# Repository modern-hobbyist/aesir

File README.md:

# Project Aesir: Custom Keyboard PCB Designs

> ** Many of these boards are still works in progress **

**Project Aesir** is a collection of custom keyboard PCB designs created using KiCad, aimed at keyboard enthusiasts and DIY makers. Each project in this collection was designed to scratch a specific itch, fill a need, or address a particular problem I had with traditional mechanical keyboards, from a template for a standard keyboard PCB using the STM32F072CBT6 microcontroller to a split ergonomic keyboard design with a modular numpad.

I initially started this collection as a personal respository of templates to get my new projects on the ground running faster, but it has gradually grown to include several board designs I've completed. Make sure to check back in periodically as I add new boards to my collection!

## Included Projects
1. **Heimdall**: A full-sized keyboard PCB designed for customization and personal use.
2. **Hermod**: A split ergonomic keyboard design for those seeking an ergonomic, portable build. Featuring a magnetically detachable AND reversible numpad!
3. **Hermod Mk. II**: A remake of the original Hermod with an upgraded STM32G474CET6 MCU, supporting Choc V2 and Gateron KS-33 low profile switches. Including an updated thumb cluster for better ergonomics and an extra key.
3. **Hermod Mk. II - MX**: A remake of the original Hermod, this time with **MX Spacing**. Same as *8Hermod Mk. II** -- supporting Choc V2 and Gateron KS-33 switches.
4. **Hermod Mk. II - MX - North**: Same as **Hermod Mk. II - MX** but with North facing switches for better shine through keycap legend appearance.
5. **Hermod Mk. III**: A continuation of **Hermod Mk. II - MX - North** with several component upgrades for easier/cheaper sourcing (e.g. SRV05-4 for ESD).
6. **Mist**: A full sized keyboard with a new take on the spacebar--replacing it with thumb clusters. It also supports Cherry MX/Gateron Normal Profile or Gateron KS-33 Low Profile Switches.
7. **Mist UDB**: Same as **Mist**, but using a unified daughter board to offload the ESD and USB protection.
8. **Mist UDB - Mk. II**: Same as **Mist UDB** but with proper support for the Gateron Low profile stabilizers as well as standard PCB mount stabilizers via mousebitten PCB cutouts.
3. **STM32F072CBT6 Standard Template**: A blank template for creating your own keyboard designs with the STM32F072CBT6 microcontroller.
4. **STM32F072CBT6 Split Template**: A blank template for creating your own split keyboard designs with the STM32F072CBT6 microcontroller.

## Getting Started

> Note: There may be footprints I've created or manually altered that aren't packaged with this repository, so if you come across something missing, please create an issue and I'll get it updated!

### Requirements
- **KiCad**: Download and install the latest version of [KiCad](https://www.kicad.org/download/).
- **PCB Manufacturer**: These projects were developed in collaboration with PCBWay. Each sub-project will have a link to the project on PCBWay's project sharing platform so you can order them with the click of a button.
- **Plugins**: There are a few KiCad plugins that you can install that will help with building these PCB's as well as one library of keyswitches:
  - [marbastlib Keyswitch Symbol Library](https://github.com/ebastler/marbastlib)
  - [kicad-kbplacer](https://github.com/adamws/kicad-kbplacer)
  - [PCBWay Order Plugin](https://github.com/pcbway/PCBWay-Plug-in-for-Kicad)

### Steps
1. Clone this repository to your local machine.
    ```bash
    git clone https://github.com/modern-hobbyist/aesir
    ```
2. Open the desired KiCad project in your KiCad software.
3. Customize the layout, add your own components, and make any modifications to fit your needs.
4. Export the Gerber files for your chosen PCB manufacturer.
5. Build and assemble your keyboard!

## Contributing
Contributions to **Project Aesir** are welcome! Whether it's improving existing designs, adding new features, or creating entirely new layouts, feel free to open a pull request.

### Contribution Guidelines
1. Fork the repository.
2. Make your changes on a new branch.
3. Submit a pull request with a clear description of your contribution.

## Disclaimer
These designs are provided as-is, without warranty of any kind. I am not liable for any damages, malfunctions, or issues that may arise from using or modifying these designs, including but not limited to hardware damage, injury, or other unintended consequences. By using these designs, you agree to take full responsibility for any results, modifications, or assembly errors.

## License
This project is licensed under the MIT License. See the [LICENSE](LICENSE) file for details.

## Contact
For questions or collaboration inquiries, feel free to create an issue, reach out to me on GitHub or Discord or via my [YouTube channel](https://www.youtube.com/ModernHobbyist).

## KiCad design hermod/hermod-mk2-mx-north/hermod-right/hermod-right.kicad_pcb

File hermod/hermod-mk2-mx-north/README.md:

# Hermod Mk. II - North

> **Note:** This PCB is untested. I made updates to this design to address issues I had with the previous version, but I haven't ordered boards, nor have I written the matching firmware for it.

Hermod Mk. II is a redesign of my original Hermod split keyboard, which in turn was my second keyboard design ever! Some issues that were resolved in this version include:
- Better Pin choices for PWM Channels, Mk. I had some issues with timers overlapping
- Added a handedness pin 
  - Allows me to avoid using flash to store handedness
- Switched to Full Duplex split comms
- Mk.I was missing a 5.1kΩ resistor on the split serial line and this switched fixes that.
- Switched to `STM32G474CETx` from the `STM32F072CBT6`
  - More Ram, more flash, more fun. Didn't have enough ram for fun graphics on the LCD
- Added PWM Backlight control for the LCD Display 

Furthermore, this is the **NORTH FACING** MX Spacing variant. While it is functionally identically to the Hermod Mk. II, this layout is spaced in a 19.05x19.05 grid, which makes it compatible with the [Tai-Hao keycaps](https://shop.tai-hao.com/products/98white-1) highlighted in the ZSA Voyager. Also, the switches are rotated 180• from the previous versions so that the LED's are better aligned with shine-through keycaps. 

## Features

- **Split Design**: Ergonomic split layout for improved typing comfort.
- **Detachable Numpad**: Magnetically detachable and reversible numpad that can connect to either half.
- **Dual LCD Displays**: Each half features a 2.2" LCD for customizable graphics and real-time information.
- **QMK Firmware**: Fully programmable and customizable using QMK.
- **Per-Key RGB Lighting**: Vibrant, individually addressable RGB LEDs for endless customization.
- **Hot-Swappable Switch Sockets**: Easily swap out switches without soldering.
- **Open Source Hardware**: Schematics and design files available for personal customization.

## Specifications

- **Microcontroller**: STM32G474CETx
- **Key Layout**: Split layout with additional keys for layers and macros.
- **Display**: 2.2" LCD (320x240 resolution) per half.
- **Lighting**: SK6812 Mini RGB LEDs.
- **Switches**: Kailh Choc Low Profile.

## Issues
- 1.5u Footprint Solder Mask Layer missing (fixed)
  - Caused one of the pads for the 1.5u switches to be covered with Solder Mask
- LCD SD Card Pins Intersecting USB Data lines (fixed)
  - I accidentally updated the LCD footprint and didn't run DRC so the data lines had LCD SD card pins running right through them.

## License

This project is licensed under the MIT License. See the [LICENSE](../LICENSE) file for details.

## Acknowledgments

- The QMK community for their amazing firmware.
- Adafruit for the GFX library support.
- Inspiration from the mechanical keyboard enthusiast community.

---

For more information, check out the [Modern Hobbyist YouTube channel](https://www.youtube.com/ModernHobbyist) for videos about this project!

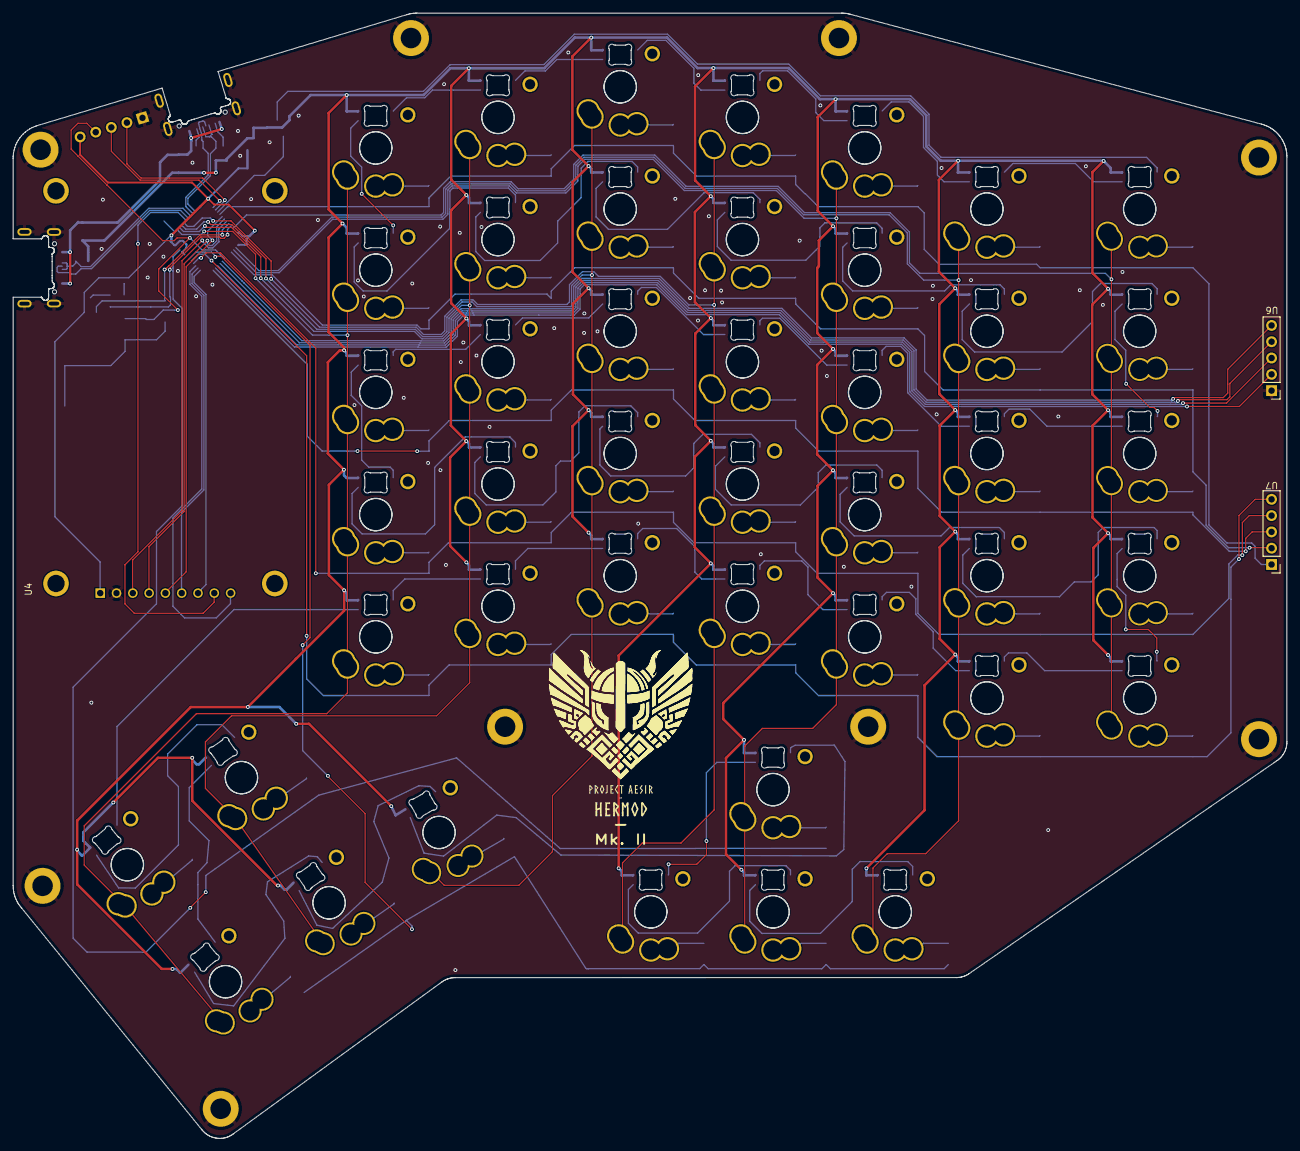
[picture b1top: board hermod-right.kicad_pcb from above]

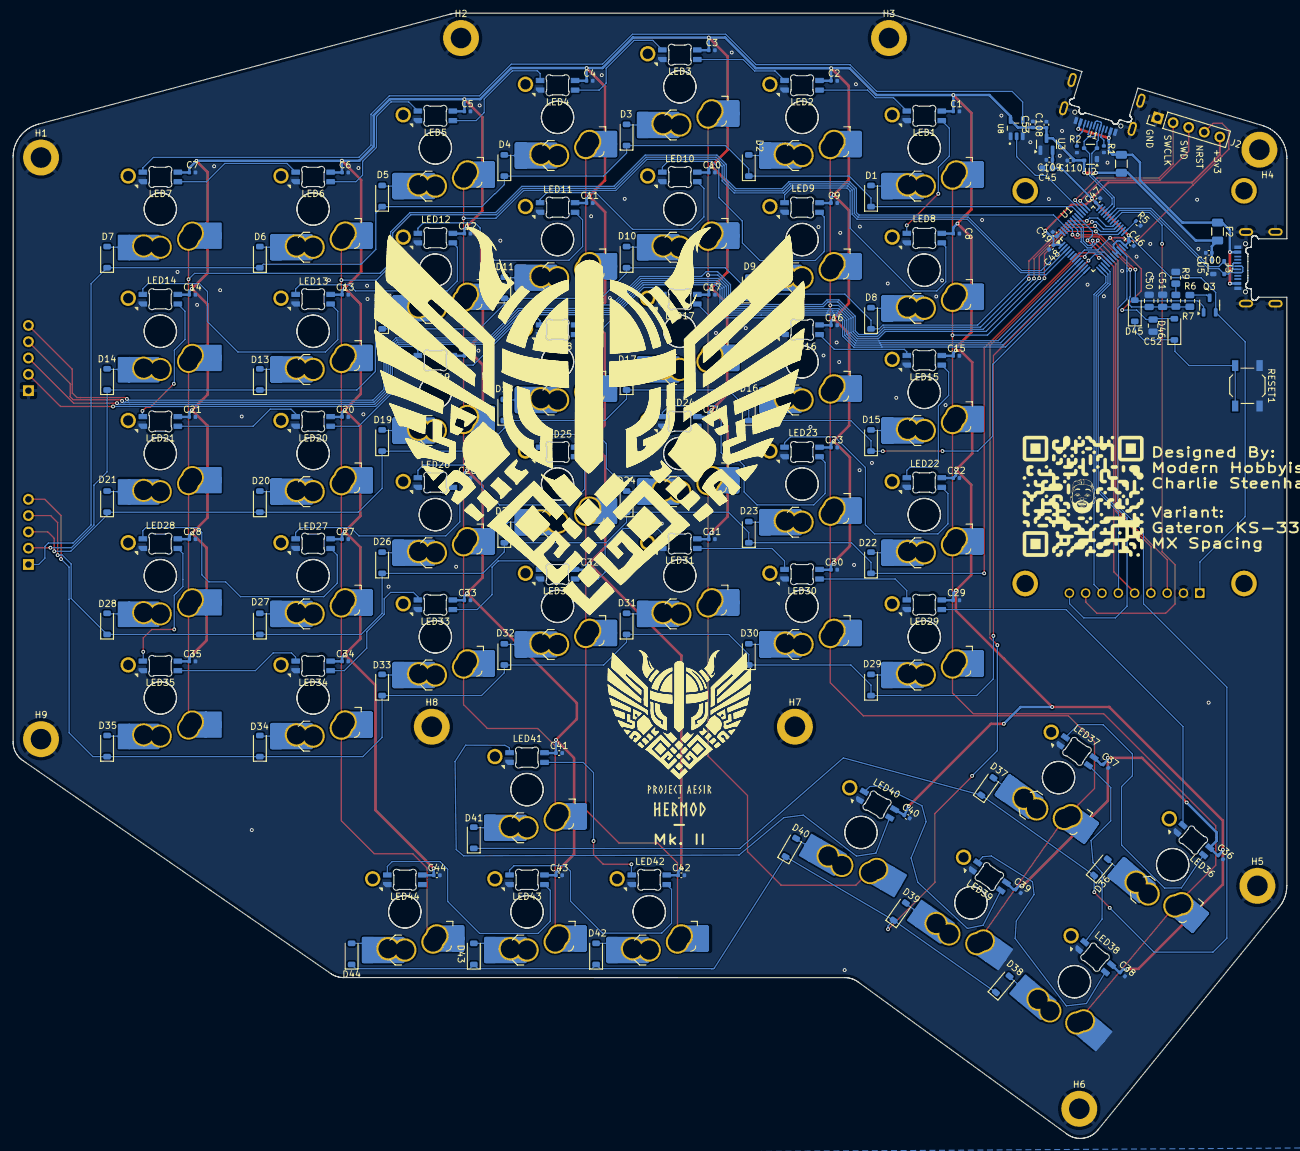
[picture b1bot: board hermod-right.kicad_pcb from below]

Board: 2 copper layers, 198.5 x 175.4 mm, 221 parts (218 on the bottom side), 133 nets.

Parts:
C1, C2, C3, C4, C5, C6, C7, C8, C9, C10, C11, C12, C13, C14, C15, C16, C17, C18, C19, C20, C21, C22, C23, C24, C25, C26, C27, C28, C29, C30, C31, C32, C33, C34, C35, C36, C37, C38, C39, C40, C41, C42, C43, C44, C53: 0.1uF; C_0402_1005Metric
C45: 10uF; C_0603_1608Metric
C46, C47, C48, C49, C100, C110: 100nF; C_0402_1005Metric
C50, C51, C52: 100n; C_0805_2012Metric
C108, C109: 1uF; C_0402_1005Metric
CH1, CH2, CH3, CH4, CH5, CH6, CH8, CH9, CH10, CH11, CH12, CH13, CH15, CH16, CH17, CH18, CH19, CH20, CH22, CH23, CH24, CH25, CH26, CH27, CH29, CH30, CH31, CH32, CH33, CH34, CH36, CH37, CH41, CH42, CH43, CH44: KS33_SW_solder; KS33_Choc-v2_HS_1U
CH7, CH14, CH21, CH28, CH35, CH38, CH39, CH40: KS33_SW_solder; KS33_Choc-v2_HS_1.5U
D1, D2, D3, D4, D5, D6, D7, D8, D9, D10, D11, D12, D13, D14, D15, D16, D17, D18, D19, D20, D21, D22, D23, D24, D25, D26, D27, D28, D29, D30, D31, D32, D33, D34, D35, D36, D37, D38, D39, D40, D41, D42, D43, D44: D; D_SOD-123
D45, D46: 1N4148; D_SOD-123
F1, F2: 500mA; Fuse_1206_3216Metric
H1, H2, H3, H4, H5, H6, H7, H8, H9: MountingHole_Pad; MountingHole_3.2mm_M3_DIN965_Pad
J1, J3: USB_C_Receptacle_USB2.0; USB_C_Receptacle_HRO_TYPE-C-31-M-14
J2: Conn_01x05; PinHeader_1x05_P2.54mm_Vertical
LED1, LED2, LED3, LED4, LED5, LED6, LED7, LED8, LED9, LED10, LED11, LED12, LED13, LED14, LED15, LED16, LED17, LED18, LED19, LED20, LED21, LED22, LED23, LED24, LED25, LED26, LED27, LED28, LED29, LED30, LED31, LED32, LED33, LED34, LED35, LED36, LED37, LED38, LED39, LED40, LED41, LED42, LED43, LED44: choc_SK6812MINI-E; LED_choc_6028R
Q3: MMUN2133LT1G; SOT-23-3
R1, R2, R5: 5.1k; R_0402_1005Metric
R6: 120; R_0805_2012Metric
R7, R9: 68k; R_0805_2012Metric
RESET1: DFU; SW_SPST_TL3342
U1: STM32G474CETx; LQFP-48_7x7mm_P0.5mm
U2, U5: PRTR5V0U2X; SOT-143
U3: XC6206PxxxMR-Regulator_Linear; SOT-23
U4: CR2013-MI2120
U6, U7: Pogo_2.54mm_5p
U8: SN74AHCT1G125DBVR; SOT95P280X145-5N

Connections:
+3V3: C45.1, C46.1, C47.1, C48.1, C49.1, C109.1, J2.5, Q3.2 (E), U1.1 (VBAT), U1.20 (VREF+), U1.21 (VDDA), U1.24 (VDD), U1.36 (VDD), U1.48 (VDD), U3.2 (VO), U4.1 (VCC)
+5V: C1.1, C2.1, C3.1, C4.1, C5.1, C6.1, C7.1, C8.1, C9.1, C10.1, C11.1, C12.1, C13.1, C14.1, C15.1, C16.1, C17.1, C18.1, C19.1, C20.1, C21.1, C22.1, C23.1, C24.1, C25.1, C26.1, C27.1, C28.1, C29.1, C30.1, C31.1, C32.1, C33.1, C34.1, C35.1, C36.1, C37.1, C38.1, C39.1, C40.1, C41.1, C42.1, C43.1, C44.1, C53.1, C100.1, C108.1, C110.1, F1.2, F2.2, LED1.1 (VDD), LED2.1 (VDD), LED3.1 (VDD), LED4.1 (VDD), LED5.1 (VDD), LED6.1 (VDD), LED7.1 (VDD), LED8.1 (VDD), LED9.1 (VDD), LED10.1 (VDD), LED11.1 (VDD), LED12.1 (VDD), LED13.1 (VDD), LED14.1 (VDD), LED15.1 (VDD), LED16.1 (VDD), LED17.1 (VDD), LED18.1 (VDD), LED19.1 (VDD), LED20.1 (VDD), LED21.1 (VDD), LED22.1 (VDD), LED23.1 (VDD), LED24.1 (VDD), LED25.1 (VDD), LED26.1 (VDD), LED27.1 (VDD), LED28.1 (VDD), LED29.1 (VDD), LED30.1 (VDD), LED31.1 (VDD), LED32.1 (VDD), LED33.1 (VDD), LED34.1 (VDD), LED35.1 (VDD), LED36.1 (VDD), LED37.1 (VDD), LED38.1 (VDD), LED39.1 (VDD), LED40.1 (VDD), LED41.1 (VDD), LED42.1 (VDD), LED43.1 (VDD), LED44.1 (VDD), U2.4 (VCC), U3.3 (VI), U5.4 (VCC), U8.5 (VCC)
BOOT0: C50.2, C51.2, R6.2, R7.2, U1.45 (PB8)
BOOT0_CHRG: D45.2 (A), Q3.1 (B), U1.44 (PB7)
D+: J1.A6 (D+), J1.B6 (D+), U1.34 (PA12), U2.3 (I/O2)
D-: J1.A7 (D-), J1.B7 (D-), U1.33 (PA11), U2.2 (I/O1)
DOut1: LED1.2 (DOUT), LED8.3 (DIN)
DOut2: LED14.2 (DOUT), LED21.3 (DIN)
DOut3: LED15.2 (DOUT), LED22.3 (DIN)
DOut4: LED28.2 (DOUT), LED35.3 (DIN)
DOut5: LED29.2 (DOUT), LED36.3 (DIN)
GND: C1.2, C2.2, C3.2, C4.2, C5.2, C6.2, C7.2, C8.2, C9.2, C10.2, C11.2, C12.2, C13.2, C14.2, C15.2, C16.2, C17.2, C18.2, C19.2, C20.2, C21.2, C22.2, C23.2, C24.2, C25.2, C26.2, C27.2, C28.2, C29.2, C30.2, C31.2, C32.2, C33.2, C34.2, C35.2, C36.2, C37.2, C38.2, C39.2, C40.2, C41.2, C42.2, C43.2, C44.2, C45.2, C46.2, C47.2, C48.2, C49.2, C50.1, C51.1, C52.1, C53.2, C100.2, C108.2, C109.2, C110.2, H1.1, H2.1, H3.1, H4.1, H5.1, H6.1, H7.1, H8.1, H9.1, J1.A1 (GND), J1.A12 (GND), J1.B1 (GND), J1.B12 (GND), J1.S1 (SHIELD), J2.1, J3.A1 (GND), J3.A12 (GND), J3.B1 (GND), J3.B12 (GND), J3.S1 (SHIELD), LED1.4 (VSS), LED2.4 (VSS), LED3.4 (VSS), LED4.4 (VSS), LED5.4 (VSS), LED6.4 (VSS), LED7.4 (VSS), LED8.4 (VSS), LED9.4 (VSS), LED10.4 (VSS), LED11.4 (VSS), LED12.4 (VSS), LED13.4 (VSS), LED14.4 (VSS), LED15.4 (VSS), LED16.4 (VSS), LED17.4 (VSS), LED18.4 (VSS), LED19.4 (VSS), LED20.4 (VSS), LED21.4 (VSS), LED22.4 (VSS), LED23.4 (VSS), LED24.4 (VSS), LED25.4 (VSS), LED26.4 (VSS), LED27.4 (VSS), LED28.4 (VSS), LED29.4 (VSS), LED30.4 (VSS), LED31.4 (VSS), LED32.4 (VSS), LED33.4 (VSS), LED34.4 (VSS), LED35.4 (VSS), LED36.4 (VSS), LED37.4 (VSS), LED38.4 (VSS), LED39.4 (VSS), LED40.4 (VSS), LED41.4 (VSS), LED42.4 (VSS), LED43.4 (VSS), LED44.4 (VSS), R1.1, R2.2, R5.2, R9.2, RESET1.1, U1.19 (VSSA), U1.23 (VSS), U1.35 (VSS), U1.47 (VSS), U2.1 (GND), U3.1 (GND), U4.2 (GND), U5.1 (GND), U6.1, U8.1 (~OE), U8.3 (GND)
HAND_PIN: R5.1, U1.25 (PB11)
LCD_BL_PWM: U1.30 (PA8), U4.8 (LED)
LCD_CS: U1.43 (PB6), U4.3 (~CS)
LCD_DC: U1.41 (PB4), U4.5 (D/~C)
LCD_MISO: U1.15 (PA7), U4.9 (MISO)
LCD_MOSI: U1.14 (PA6), U4.6 (MOSI)
LCD_RST: U1.42 (PB5), U4.4 (RESET)
LCD_SCK: U1.13 (PA5), U4.7 (SCK)
NRST: C52.2, D46.2 (A), J2.4, U1.7 (PG10)
unnamed: CH1.2, D1.2 (A)
unnamed: CH2.2, D2.2 (A)
unnamed: CH3.2, D3.2 (A)
unnamed: CH4.2, D4.2 (A)
unnamed: CH5.2, D5.2 (A)
unnamed: CH6.2, D6.2 (A)
unnamed: CH7.2, D7.2 (A)
unnamed: CH8.2, D8.2 (A)
unnamed: CH9.2, D9.2 (A)
unnamed: CH10.2, D10.2 (A)
unnamed: CH11.2, D11.2 (A)
unnamed: CH12.2, D12.2 (A)
unnamed: CH13.2, D13.2 (A)
unnamed: CH14.2, D14.2 (A)
unnamed: CH15.2, D15.2 (A)
unnamed: CH16.2, D16.2 (A)
unnamed: CH17.2, D17.2 (A)
unnamed: CH18.2, D18.2 (A)
unnamed: CH19.2, D19.2 (A)
unnamed: CH20.2, D20.2 (A)
unnamed: CH21.2, D21.2 (A)
unnamed: CH22.2, D22.2 (A)
unnamed: CH23.2, D23.2 (A)
unnamed: CH24.2, D24.2 (A)
unnamed: CH25.2, D25.2 (A)
unnamed: CH26.2, D26.2 (A)
unnamed: CH27.2, D27.2 (A)
unnamed: CH28.2, D28.2 (A)
unnamed: CH29.2, D29.2 (A)
unnamed: CH30.2, D30.2 (A)
unnamed: CH31.2, D31.2 (A)
unnamed: CH32.2, D32.2 (A)
unnamed: CH33.2, D33.2 (A)
unnamed: CH34.2, D34.2 (A)
unnamed: CH35.2, D35.2 (A)
unnamed: CH36.2, D36.2 (A)
unnamed: CH37.2, D37.2 (A)
unnamed: CH38.2, D38.2 (A)
unnamed: CH39.2, D39.2 (A)
unnamed: CH40.2, D40.2 (A)
unnamed: CH41.2, D41.2 (A)
unnamed: CH42.2, D42.2 (A)
unnamed: CH43.2, D43.2 (A)
unnamed: CH44.2, D44.2 (A)
unnamed: D45.1 (K), D46.1 (K), RESET1.2
unnamed: J1.A5 (CC1), R1.2
unnamed: J1.B5 (CC2), R2.1
unnamed: LED1.3 (DIN), LED2.2 (DOUT)
unnamed: LED2.3 (DIN), LED3.2 (DOUT)
unnamed: LED3.3 (DIN), LED4.2 (DOUT)
unnamed: LED4.3 (DIN), LED5.2 (DOUT)
unnamed: LED5.3 (DIN), LED6.2 (DOUT)
unnamed: LED6.3 (DIN), LED7.2 (DOUT)
unnamed: LED8.2 (DOUT), LED9.3 (DIN)
unnamed: LED9.2 (DOUT), LED10.3 (DIN)
unnamed: LED10.2 (DOUT), LED11.3 (DIN)
unnamed: LED11.2 (DOUT), LED12.3 (DIN)
unnamed: LED12.2 (DOUT), LED13.3 (DIN)
unnamed: LED13.2 (DOUT), LED14.3 (DIN)
unnamed: LED15.3 (DIN), LED16.2 (DOUT)
unnamed: LED16.3 (DIN), LED17.2 (DOUT)
unnamed: LED17.3 (DIN), LED18.2 (DOUT)
unnamed: LED18.3 (DIN), LED19.2 (DOUT)
unnamed: LED19.3 (DIN), LED20.2 (DOUT)
unnamed: LED20.3 (DIN), LED21.2 (DOUT)
unnamed: LED22.2 (DOUT), LED23.3 (DIN)
unnamed: LED23.2 (DOUT), LED24.3 (DIN)
unnamed: LED24.2 (DOUT), LED25.3 (DIN)
unnamed: LED25.2 (DOUT), LED26.3 (DIN)
unnamed: LED26.2 (DOUT), LED27.3 (DIN)
unnamed: LED27.2 (DOUT), LED28.3 (DIN)
unnamed: LED29.3 (DIN), LED30.2 (DOUT)
unnamed: LED30.3 (DIN), LED31.2 (DOUT)
unnamed: LED31.3 (DIN), LED32.2 (DOUT)
unnamed: LED32.3 (DIN), LED33.2 (DOUT)
unnamed: LED33.3 (DIN), LED34.2 (DOUT)
unnamed: LED34.3 (DIN), LED35.2 (DOUT)
unnamed: LED36.2 (DOUT), LED37.3 (DIN)
unnamed: LED37.2 (DOUT), LED38.3 (DIN)
unnamed: LED38.2 (DOUT), LED39.3 (DIN)
unnamed: LED39.2 (DOUT), LED40.3 (DIN)
unnamed: LED40.2 (DOUT), LED41.3 (DIN)
unnamed: LED41.2 (DOUT), LED42.3 (DIN)
unnamed: LED42.2 (DOUT), LED43.3 (DIN)
unnamed: LED43.2 (DOUT), LED44.3 (DIN)
unnamed: Q3.3 (C), R6.1
unnamed: R7.1, R9.1
RGB3.3: U1.39 (PA15), U8.2 (A)
RGB5v: LED7.3 (DIN), U8.4 (Y)
SWCLK: J2.2, U1.38 (PA14)
SWD: J2.3, U1.37 (PA13)
SplitSerial-RX: J3.A6 (D+), J3.B6 (D+), U1.32 (PA10), U5.3 (I/O2)
SplitSerial-TX: J3.A7 (D-), J3.B7 (D-), U1.31 (PA9), U5.2 (I/O1)
VBUS: F1.1, F2.1, J1.A4 (VBUS), J1.A9 (VBUS), J1.B4 (VBUS), J1.B9 (VBUS), J3.A4 (VBUS), J3.A9 (VBUS), J3.B4 (VBUS), J3.B9 (VBUS)
col0: CH1.1, CH8.1, CH15.1, CH22.1, CH29.1, CH36.1, CH38.1, U1.26 (PB12)
col1: CH2.1, CH9.1, CH16.1, CH23.1, CH30.1, CH37.1, CH39.1, U1.27 (PB13)
col2: CH3.1, CH10.1, CH17.1, CH24.1, CH31.1, CH40.1, U1.28 (PB14)
col3: CH4.1, CH11.1, CH18.1, CH25.1, CH32.1, CH42.1, U1.29 (PB15)
col4: CH5.1, CH12.1, CH19.1, CH26.1, CH33.1, CH41.1, CH43.1, U1.3 (PC14)
col5: CH6.1, CH13.1, CH20.1, CH27.1, CH34.1, CH44.1, U1.2 (PC13)
col6: CH7.1, CH14.1, CH21.1, CH28.1, CH35.1, U1.46 (PB9)
col7: U1.8 (PA0), U6.5
col8: U1.9 (PA1), U6.4
col9: U1.10 (PA2), U6.3
col10: U1.11 (PA3), U6.2
row0: D1.1 (K), D2.1 (K), D3.1 (K), D4.1 (K), D5.1 (K), D6.1 (K), D7.1 (K), U1.40 (PB3), U7.1
row1: D8.1 (K), D9.1 (K), D10.1 (K), D11.1 (K), D12.1 (K), D13.1 (K), D14.1 (K), U1.4 (PC15), U7.2
row2: D15.1 (K), D16.1 (K), D17.1 (K), D18.1 (K), D19.1 (K), D20.1 (K), D21.1 (K), U1.12 (PA4), U7.3
row3: D22.1 (K), D23.1 (K), D24.1 (K), D25.1 (K), D26.1 (K), D27.1 (K), D28.1 (K), U1.16 (PB0), U7.4
row4: D29.1 (K), D30.1 (K), D31.1 (K), D32.1 (K), D33.1 (K), D34.1 (K), D35.1 (K), U1.17 (PB1), U7.5
row5: D36.1 (K), D37.1 (K), D41.1 (K), U1.22 (PB10)
row6: D38.1 (K), D39.1 (K), D40.1 (K), D42.1 (K), D43.1 (K), D44.1 (K), U1.18 (PB2)

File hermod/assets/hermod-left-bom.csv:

"Id";"Designator";"Footprint";"Quantity";"Designation";"Supplier and ref";
1;"U7,U6";"Pogo_2.54mm_5p";2;"~";;;
2;"U4";"CR2013-MI2120";1;"CR2013-MI2120";;;
3;"J2";"PinHeader_1x05_P2.54mm_Vertical";1;"Conn_01x05";;;
4;"CH17,CH14,CH33,CH11,CH12,CH21,CH5,CH6,CH31,CH26,CH24,CH27,CH25,CH20,CH7,CH8,CH1,CH19,CH10,CH34,CH22,CH3,CH36,CH4,CH13,CH29,CH35,CH18,CH15,CH37,CH32,CH28";"SW_choc_v1_HS_CPG135001S30_1u";32;"choc_v1_SW_HS";;;
5;"LED36,LED13,LED21,LED32,LED23,LED2,LED20,LED1,LED38,LED29,LED33,LED30,LED18,LED19,LED17,LED8,LED39,LED15,LED24,LED16,LED3,LED4,LED5,LED26,LED27,LED31,LED25,LED9,LED12,LED22,LED34,LED6,LED10,LED11,LED7,LED35,LED28,LED14,LED37";"LED_choc_6028R";39;"choc_SK6812MINI-E";;;
6;"D2,D33,D28,D20,D1,D36,D30,D22,D39,D14,D24,D13,D12,D19,D16,D25,D11,D3,D37,D15,D18,D23,D34,D21,D6,D5,D35,D4,D31,D29,D38,D10,D26,D8,D17,D7,D32,D9,D27";"D_SOD-123";39;"D";;;
7;"C106,C104,C109,C100,C102,C105,C103";"C_0402_1005Metric";7;"100nF";;;
8;"C10,C28,C19,C43,C11,C20,C34,C33,C44,C36,C23,C27,C32,C22,C21,C6,C37,C14,C3,C39,C18,C9,C7,C15,C30,C38,C24,C29,C25,C4,C26,C35,C8,C12,C16,C5,C17,C31,C1,C13,C2";"C_0402_1005Metric";41;"0.1uF";;;
9;"Q1";"SOT-23-3";1;"AO3401A";;;
10;"CH16,CH38,CH23,CH30,CH2,CH39,CH9";"SW_choc_v1_HS_CPG135001S30_1.5u";7;"choc_v1_SW_HS";;;
11;"RST1,BOOT1";"SW_SPST_TL3342";2;"SW_SPST";;;
12;"R2,R3,R1,R4";"R_0402_1005Metric";4;"5.1k";;;
13;"C101";"C_0603_1608Metric";1;"10uF";;;
14;"C107,C108";"C_0402_1005Metric";2;"1uF";;;
15;"F1";"Fuse_1206_3216Metric";1;"500mA";;;
16;"U5";"SOT-363_SC-70-6_Handsoldering";1;"TXB0101";;;
17;"U2";"SOT-143";1;"PRTR5V0U2X";;;
18;"U1";"LQFP-48_7x7mm_P0.5mm";1;"STM32F072CBT6";;;
19;"J1,J3";"USB_C_Receptacle_HRO_TYPE-C-31-M-14";2;"USB_C_Receptacle_USB2.0";;;
20;"U3";"SOT-23";1;"XC6206PxxxMR-Regulator_Linear";;;
21;"Q2";"SOT-23-3";1;"MMUN2233LT1G";;;

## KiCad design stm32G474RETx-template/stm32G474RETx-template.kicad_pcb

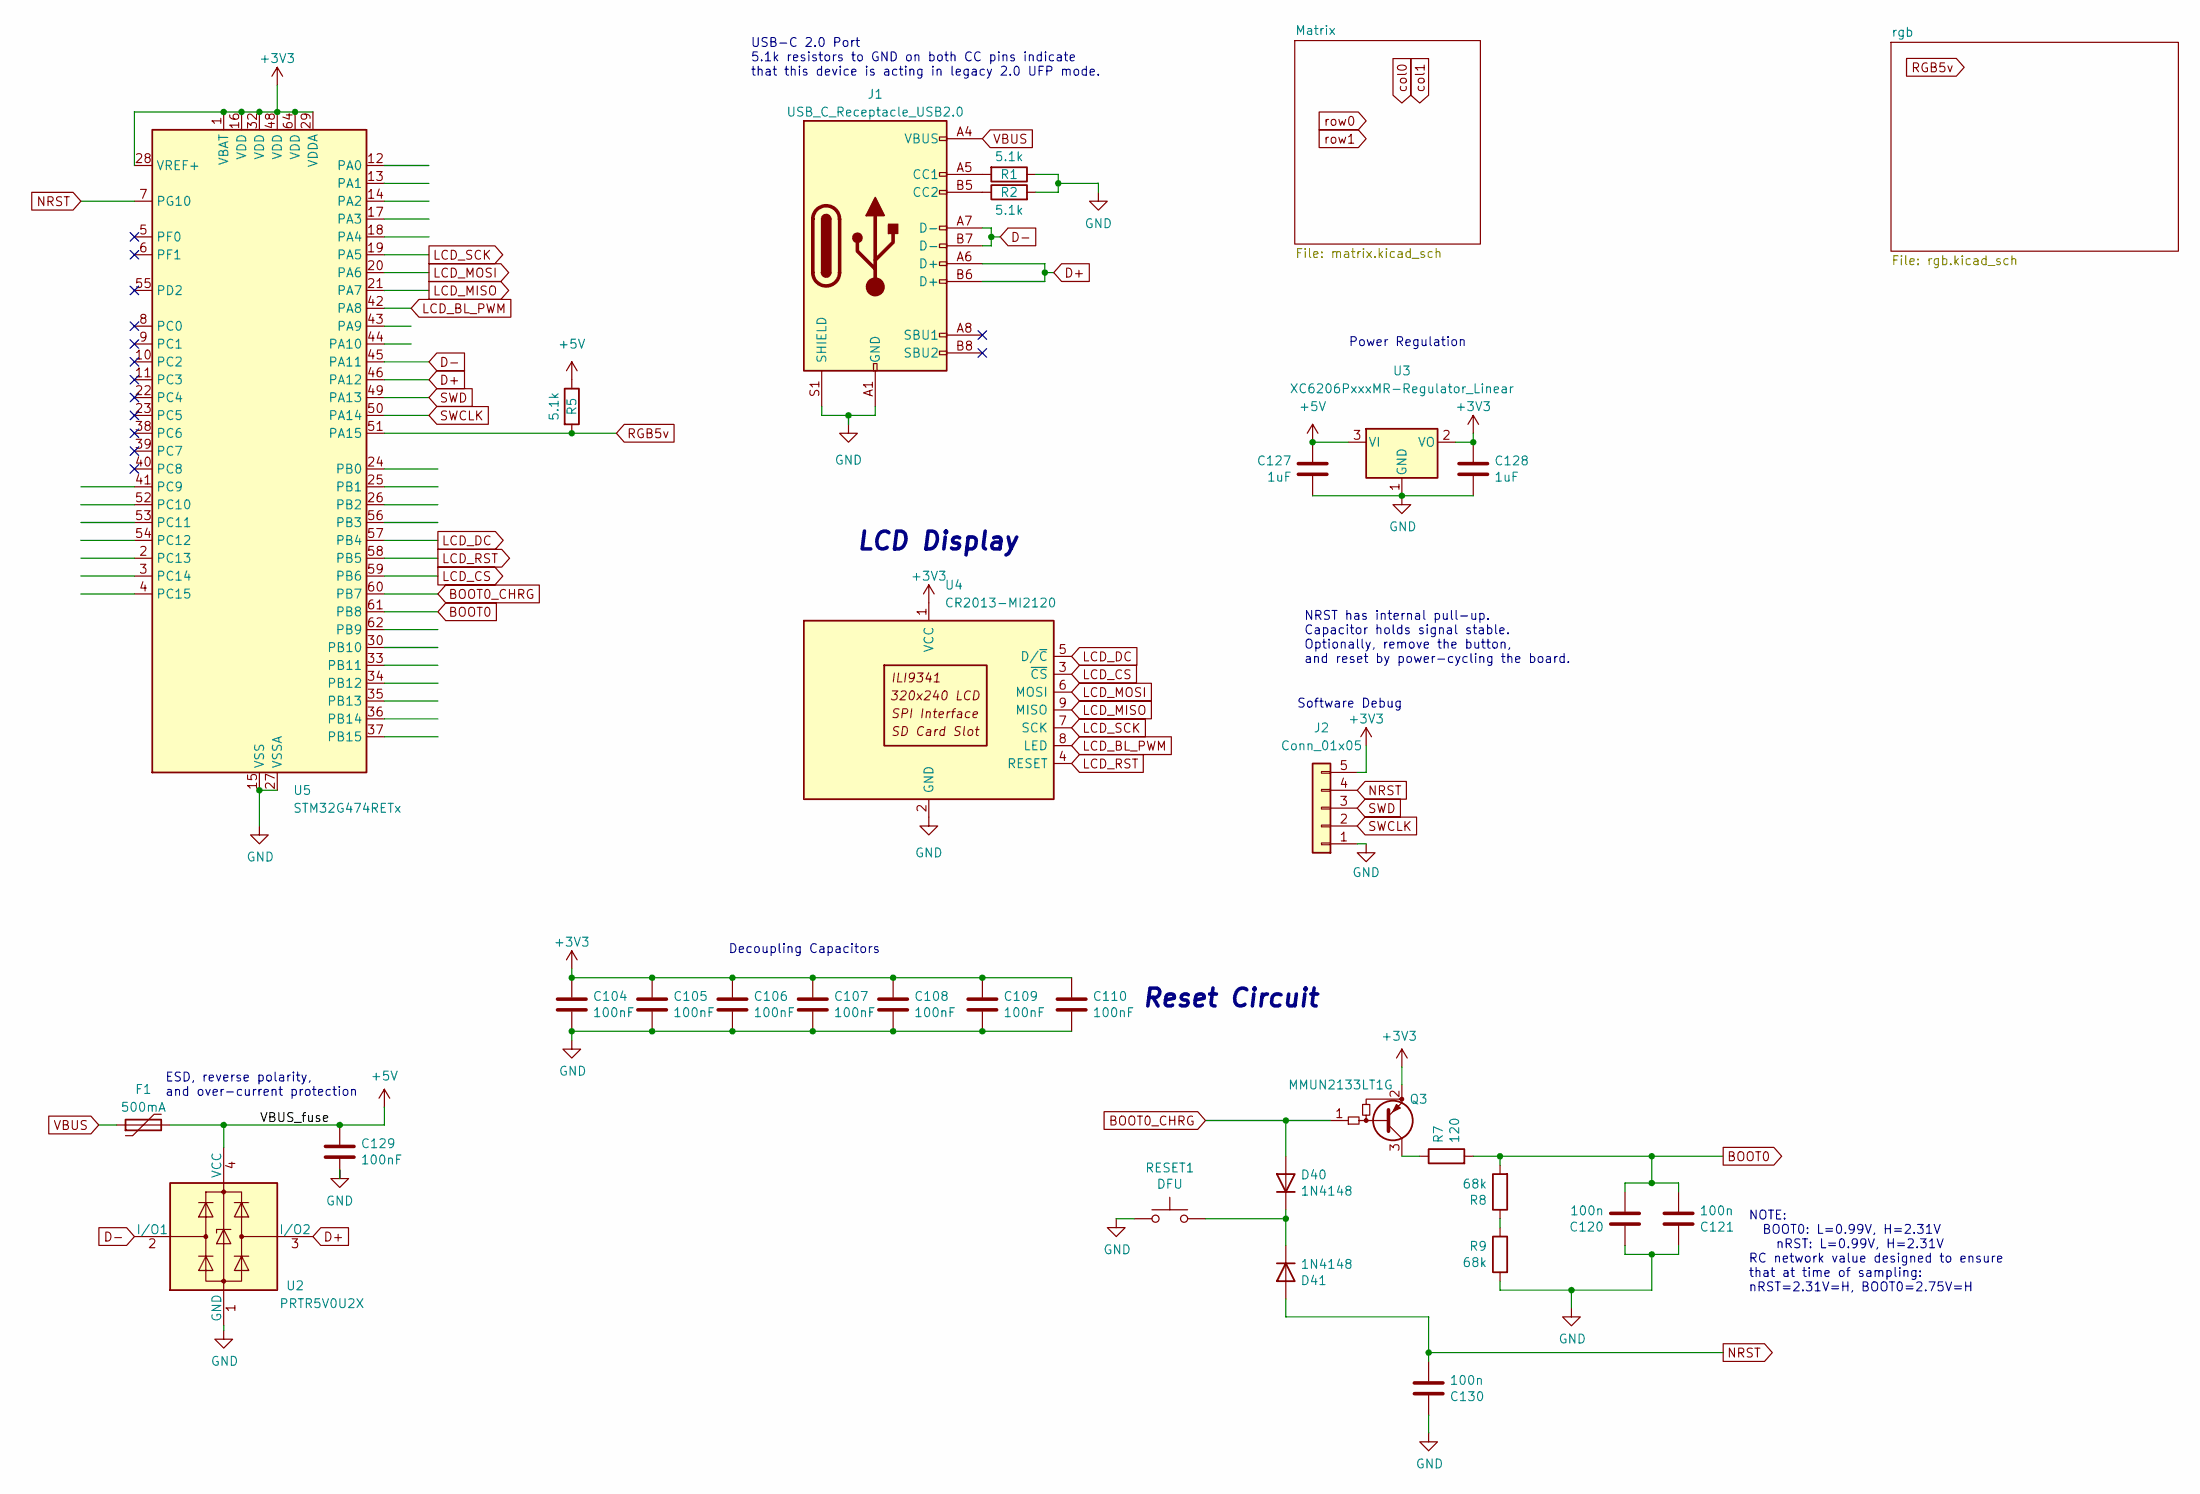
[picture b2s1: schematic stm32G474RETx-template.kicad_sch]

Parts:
C104, C105, C106, C107, C108, C109, C110, C129: 100nF; C_0402_1005Metric; LCSC C307331
C120, C121, C130: 100n; C_0805_2012Metric
C127, C128: 1uF; C_0402_1005Metric; LCSC C307331
D40, D41: 1N4148; D_SOD-123
F1: 500mA; Fuse_1206_3216Metric; LCSC C135341
J1: USB_C_Receptacle_USB2.0; USB_C_Receptacle_HRO_TYPE-C-31-M-12; JlcRotOffset 180
J2: Conn_01x05; PinHeader_1x05_P2.54mm_Vertical
Q3: MMUN2133LT1G; SOT-23-3
R1, R2, R5: 5.1k; R_0402_1005Metric
R7: 120; R_0805_2012Metric
R8, R9: 68k; R_0805_2012Metric
RESET1: DFU; SW_SPST_TL3342
U2: PRTR5V0U2X; SOT-143; LCSC C2827688
U3: XC6206PxxxMR-Regulator_Linear; SOT-23; LCSC C5446
U4: CR2013-MI2120
U5: STM32G474RETx; LQFP-64_10x10mm_P0.5mm

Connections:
+3V3: C104.1, C105.1, C106.1, C107.1, C108.1, C109.1, C110.1, C128.1, J2.5, Q3.2 (E), U3.2 (VO), U4.1 (VCC), U5.1 (VBAT), U5.16 (VDD), U5.28 (VREF+), U5.29 (VDDA), U5.32 (VDD), U5.48 (VDD), U5.64 (VDD)
+5V: C127.1, C129.1, F1.2, R5.1, U2.4 (VCC), U3.3 (VI); also elsewhere on the board
BOOT0: C120.2, C121.2, R7.2, R8.2, U5.61 (PB8)
BOOT0_CHRG: D40.2 (A), Q3.1 (B), U5.60 (PB7)
D+: J1.A6 (D+), J1.B6 (D+), U2.3 (I/O2), U5.46 (PA12)
D-: J1.A7 (D-), J1.B7 (D-), U2.2 (I/O1), U5.45 (PA11)
GND: C104.2, C105.2, C106.2, C107.2, C108.2, C109.2, C110.2, C120.1, C121.1, C127.2, C128.2, C129.2, C130.1, J1.A1 (GND), J1.A12 (GND), J1.B1 (GND), J1.B12 (GND), J1.S1 (SHIELD), J2.1, R1.1, R2.2, R9.2, RESET1.1, U2.1 (GND), U3.1 (GND), U4.2 (GND), U5.15 (VSS), U5.27 (VSSA), U5.31 (VSS), U5.47 (VSS), U5.63 (VSS); also elsewhere on the board
LCD_BL_PWM: U4.8 (LED), U5.42 (PA8)
LCD_CS: U4.3 (~CS), U5.59 (PB6)
LCD_DC: U4.5 (D/~C), U5.57 (PB4)
LCD_MISO: U4.9 (MISO), U5.21 (PA7)
LCD_MOSI: U4.6 (MOSI), U5.20 (PA6)
LCD_RST: U4.4 (RESET), U5.58 (PB5)
LCD_SCK: U4.7 (SCK), U5.19 (PA5)
NRST: C130.2, D41.2 (A), J2.4, U5.7 (PG10)
unnamed: D40.1 (K), D41.1 (K), RESET1.2
unnamed: J1.A5 (CC1), R1.2
unnamed: J1.B5 (CC2), R2.1
unnamed: Q3.3 (C), R7.1
unnamed: R8.1, R9.1
RGB5v: R5.2, U5.51 (PA15); also elsewhere on the board
SWCLK: J2.2, U5.50 (PA14)
SWD: J2.3, U5.49 (PA13)
VBUS: F1.1, J1.A4 (VBUS), J1.A9 (VBUS), J1.B4 (VBUS), J1.B9 (VBUS)

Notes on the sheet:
Decoupling Capacitors
NOTE: BOOT0: L=0.99V, H=2.31V nRST: L=0.99V, H=2.31V RC network value designed to ensure that at time of sampling: nRST=2.31V=H, BOOT0=2.75V=H
Power Regulation
Reset Circuit
USB-C 2.0 Port 5.1k resistors to GND on both CC pins indicate that this device is acting in legacy 2.0 UFP mode.
ESD, reverse polarity, and over-current protection
Software Debug
NRST has internal pull-up. Capacitor holds signal stable. Optionally, remove the button, and reset by power-cycling the board.
LCD Display

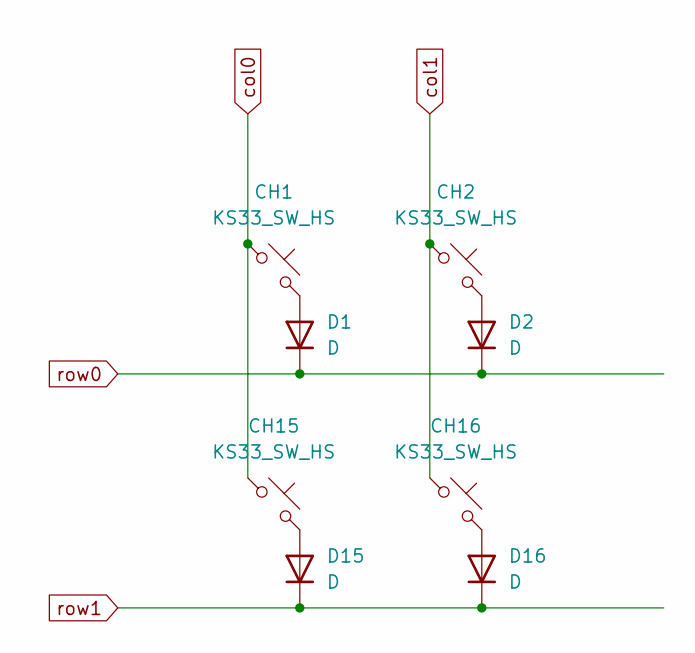
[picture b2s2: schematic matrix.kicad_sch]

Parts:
CH1, CH2, CH15, CH16: KS33_SW_HS; KS-33_MX-Hotswap-1U
D1, D2, D15, D16: D; D_SOD-123

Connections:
unnamed: CH1.2, D1.2 (A)
unnamed: CH2.2, D2.2 (A)
unnamed: CH15.2, D15.2 (A)
unnamed: CH16.2, D16.2 (A)
col0: CH1.1, CH15.1
col1: CH2.1, CH16.1
row0: D1.1 (K), D2.1 (K)
row1: D15.1 (K), D16.1 (K)

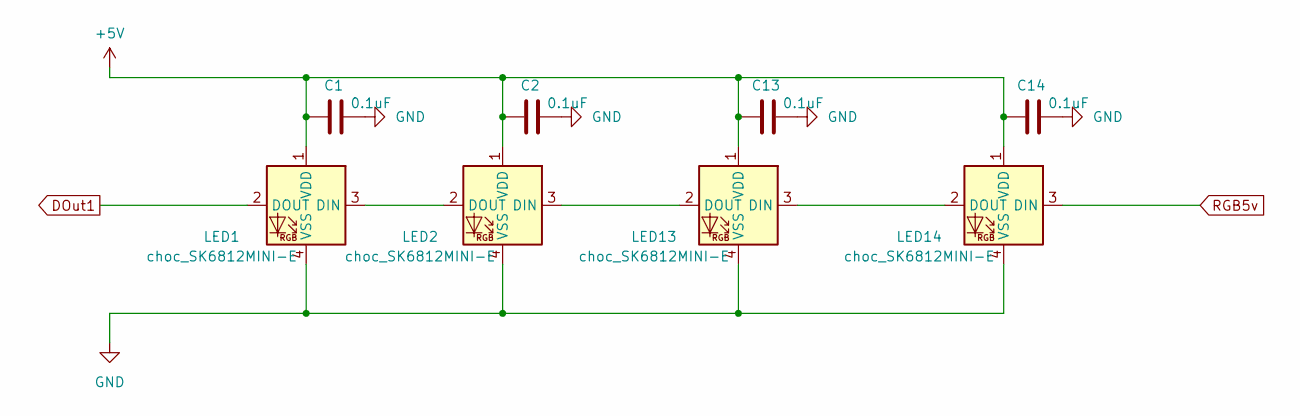
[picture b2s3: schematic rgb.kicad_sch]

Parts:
C1, C2, C13, C14: 0.1uF; C_0402_1005Metric
LED1, LED2, LED13, LED14: choc_SK6812MINI-E; LED_choc_6028R

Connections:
+5V: C1.1, C2.1, C13.1, C14.1, LED1.1 (VDD), LED2.1 (VDD), LED13.1 (VDD), LED14.1 (VDD); also elsewhere on the board
DOut1: LED1.2 (DOUT)
GND: C1.2, C2.2, C13.2, C14.2, LED1.4 (VSS), LED2.4 (VSS), LED13.4 (VSS), LED14.4 (VSS); also elsewhere on the board
unnamed: LED1.3 (DIN), LED2.2 (DOUT)
unnamed: LED13.3 (DIN), LED14.2 (DOUT)
unnamed: LED2.3 (DIN), LED13.2 (DOUT)
RGB5v: LED14.3 (DIN); also elsewhere on the board

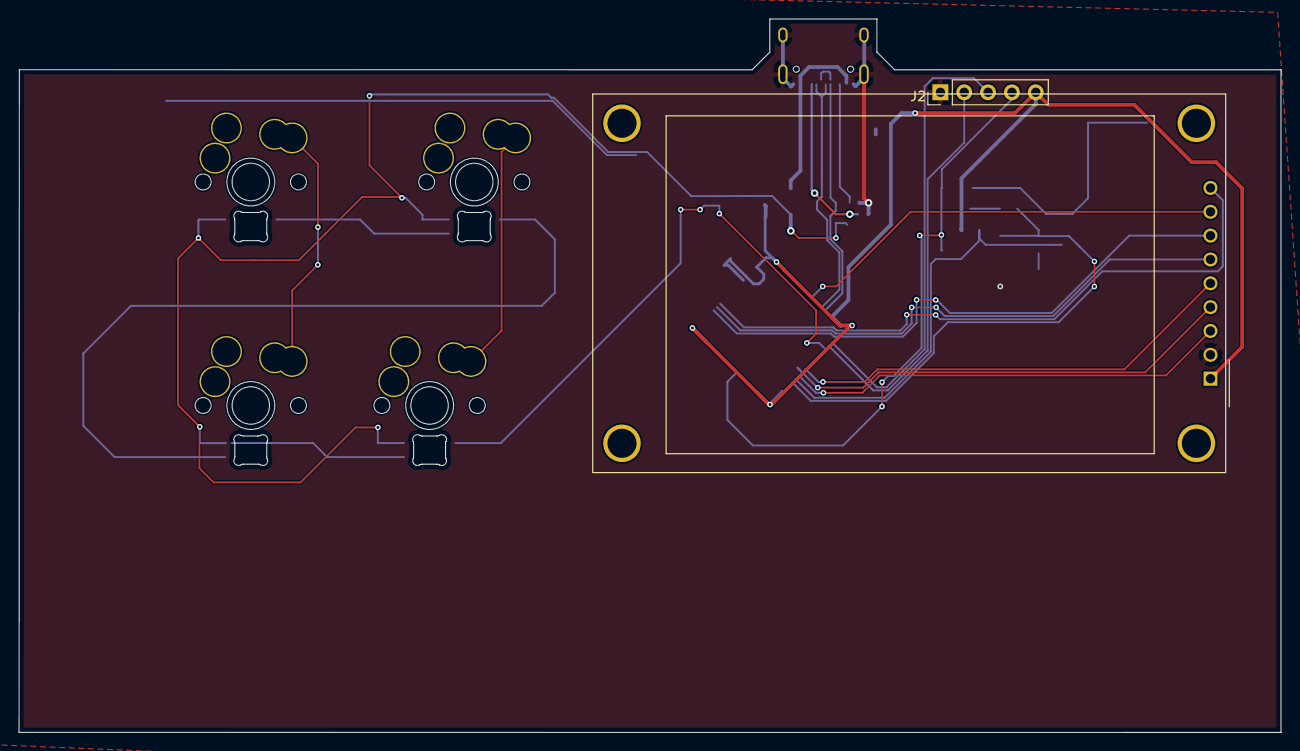
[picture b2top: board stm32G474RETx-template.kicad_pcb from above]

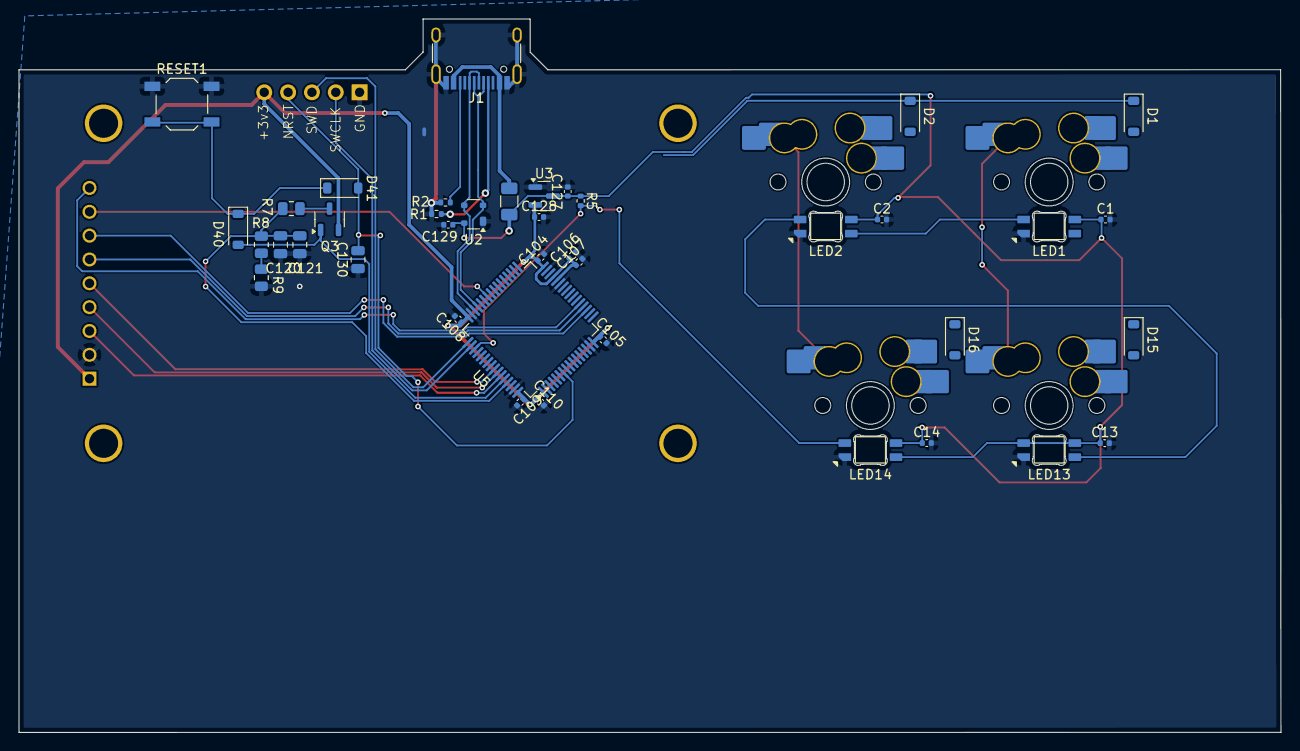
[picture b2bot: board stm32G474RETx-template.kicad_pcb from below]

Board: 2 copper layers, 134.5 x 76.0 mm, 46 parts (44 on the bottom side), 35 nets.

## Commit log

2024-09-07 Added in progress label
2024-09-08 Wired the LEDs on the right
2024-09-08 Wired up rows and cols
2024-09-08 Updated more wiring
2024-09-08 Finished wiring and addressed DRC
2024-09-08 Updated something
2024-09-09 Finished routing
2024-09-11 Added PCBWay DRC presets
2024-09-18 Fixed capacitor orientation
2024-10-30 Updated extended hermod
2024-12-27 Finished routing the left side 100%
2025-01-03 Finished hermod designs
2025-01-04 Fixed random trace on numpad
2025-01-04 Updated logos on the boards
2025-01-04 Deleted old projects and updated readme's
2025-01-04 Renamed to Hermod, added logos
2025-01-04 Added hermod readme
2025-01-04 REnamed readme
2025-01-04 Fixed license link
2025-01-04 gitignore updates
2025-01-06 Added new version for hermod
2025-01-06 Some updates
2025-01-06 Fixed up the 5v for LEDs
2025-01-09 Fixed dynamic qr code
2025-01-09 Saved heimdall
2025-01-09 Fixed some stuff
2025-01-12 Some quick updates
2025-01-13 Fixed some things
2025-01-13 More updates
2025-02-01 Fixed up hermod mk1 and updated hermod mk2
2025-02-01 Added some labels
2025-02-01 README update
2025-02-01 Updated left
2025-07-10 Updates, added UDB project
2025-07-10 Updated UDB files
2025-07-11 Updated standoff sizes
2025-07-17 Removed step files
2025-07-18 UPdated Hermod Mk 2 to have ks33 and choc v2 footprints
2025-07-18 Updated main readme
2025-07-18 Removed ground plane rule area
2025-07-19 Update og mist, updated readmes
2025-07-19 Updated gitignore
2025-07-21 Added switches to hermod 3 and updated mist thumb spacing
2025-07-21 Fixed spacing issues
2025-07-21 Fixed mist to not have rotated LEDs
2025-07-21 Cleanup, gave more space to arrow keys
2025-07-22 Mist Cleanup
2025-08-06 Fixed UDB pinout, had it backwards
2025-11-11 Updated mist project and README
2025-11-19 Removed PCBWay production folder
2025-11-20 Removes unneeded files
2025-12-01 Added north facing version of hermod and mist
2025-12-02 Finished mist north mk II
2025-12-02 Cleaned up routing for mist mk ii north
2025-12-02 Cleaned up hermod II north
2025-12-08 Lots of updates
2025-12-08 Fixed cap annotations
2025-12-09 Cleaned up mist, added better stab footprints
2025-12-09 Fixed footprints for ks33/mx stabs
2025-12-10 Updated footprint for mx/ks33 stabs again
2025-12-12 More cleanup
2025-12-18 Updated footprints for mk2-mx
2025-12-18 Added footprints
2025-12-20 Cleaned up footprints
2025-12-22 Fixed fucked up left PCB
2025-12-22 Fixed masking issue with PCBs
2025-12-23 Adjusted ILI9341 footprint 3d model
2025-12-30 Updated hermod-mk2-mx
2025-12-30 Updated numpad for hermod-mk2-mk-north
2025-12-30 Moved and organized hermod files
2025-12-31 Switched to SRV05-4
2025-12-31 Updated README for hermod mk III
2026-01-02 Revise project details in README.md
    Updated project descriptions for Hermod and Mist keyboards, including MCU specifications and ergonomic features.
2026-01-02 Added overall mist readme
